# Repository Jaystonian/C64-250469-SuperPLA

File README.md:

# C64-250469-SuperPLA
Replacement board for a 251715-01 or 252535-01

I built one to test and topically it did not work, need to find time to understand why.  I suspect it was the AHCT chips, should use HCT.

Update 2023-04-07 The problem turns out to be the PCB's footprint for the SRAM, as Pin 1 is in the wrong location.

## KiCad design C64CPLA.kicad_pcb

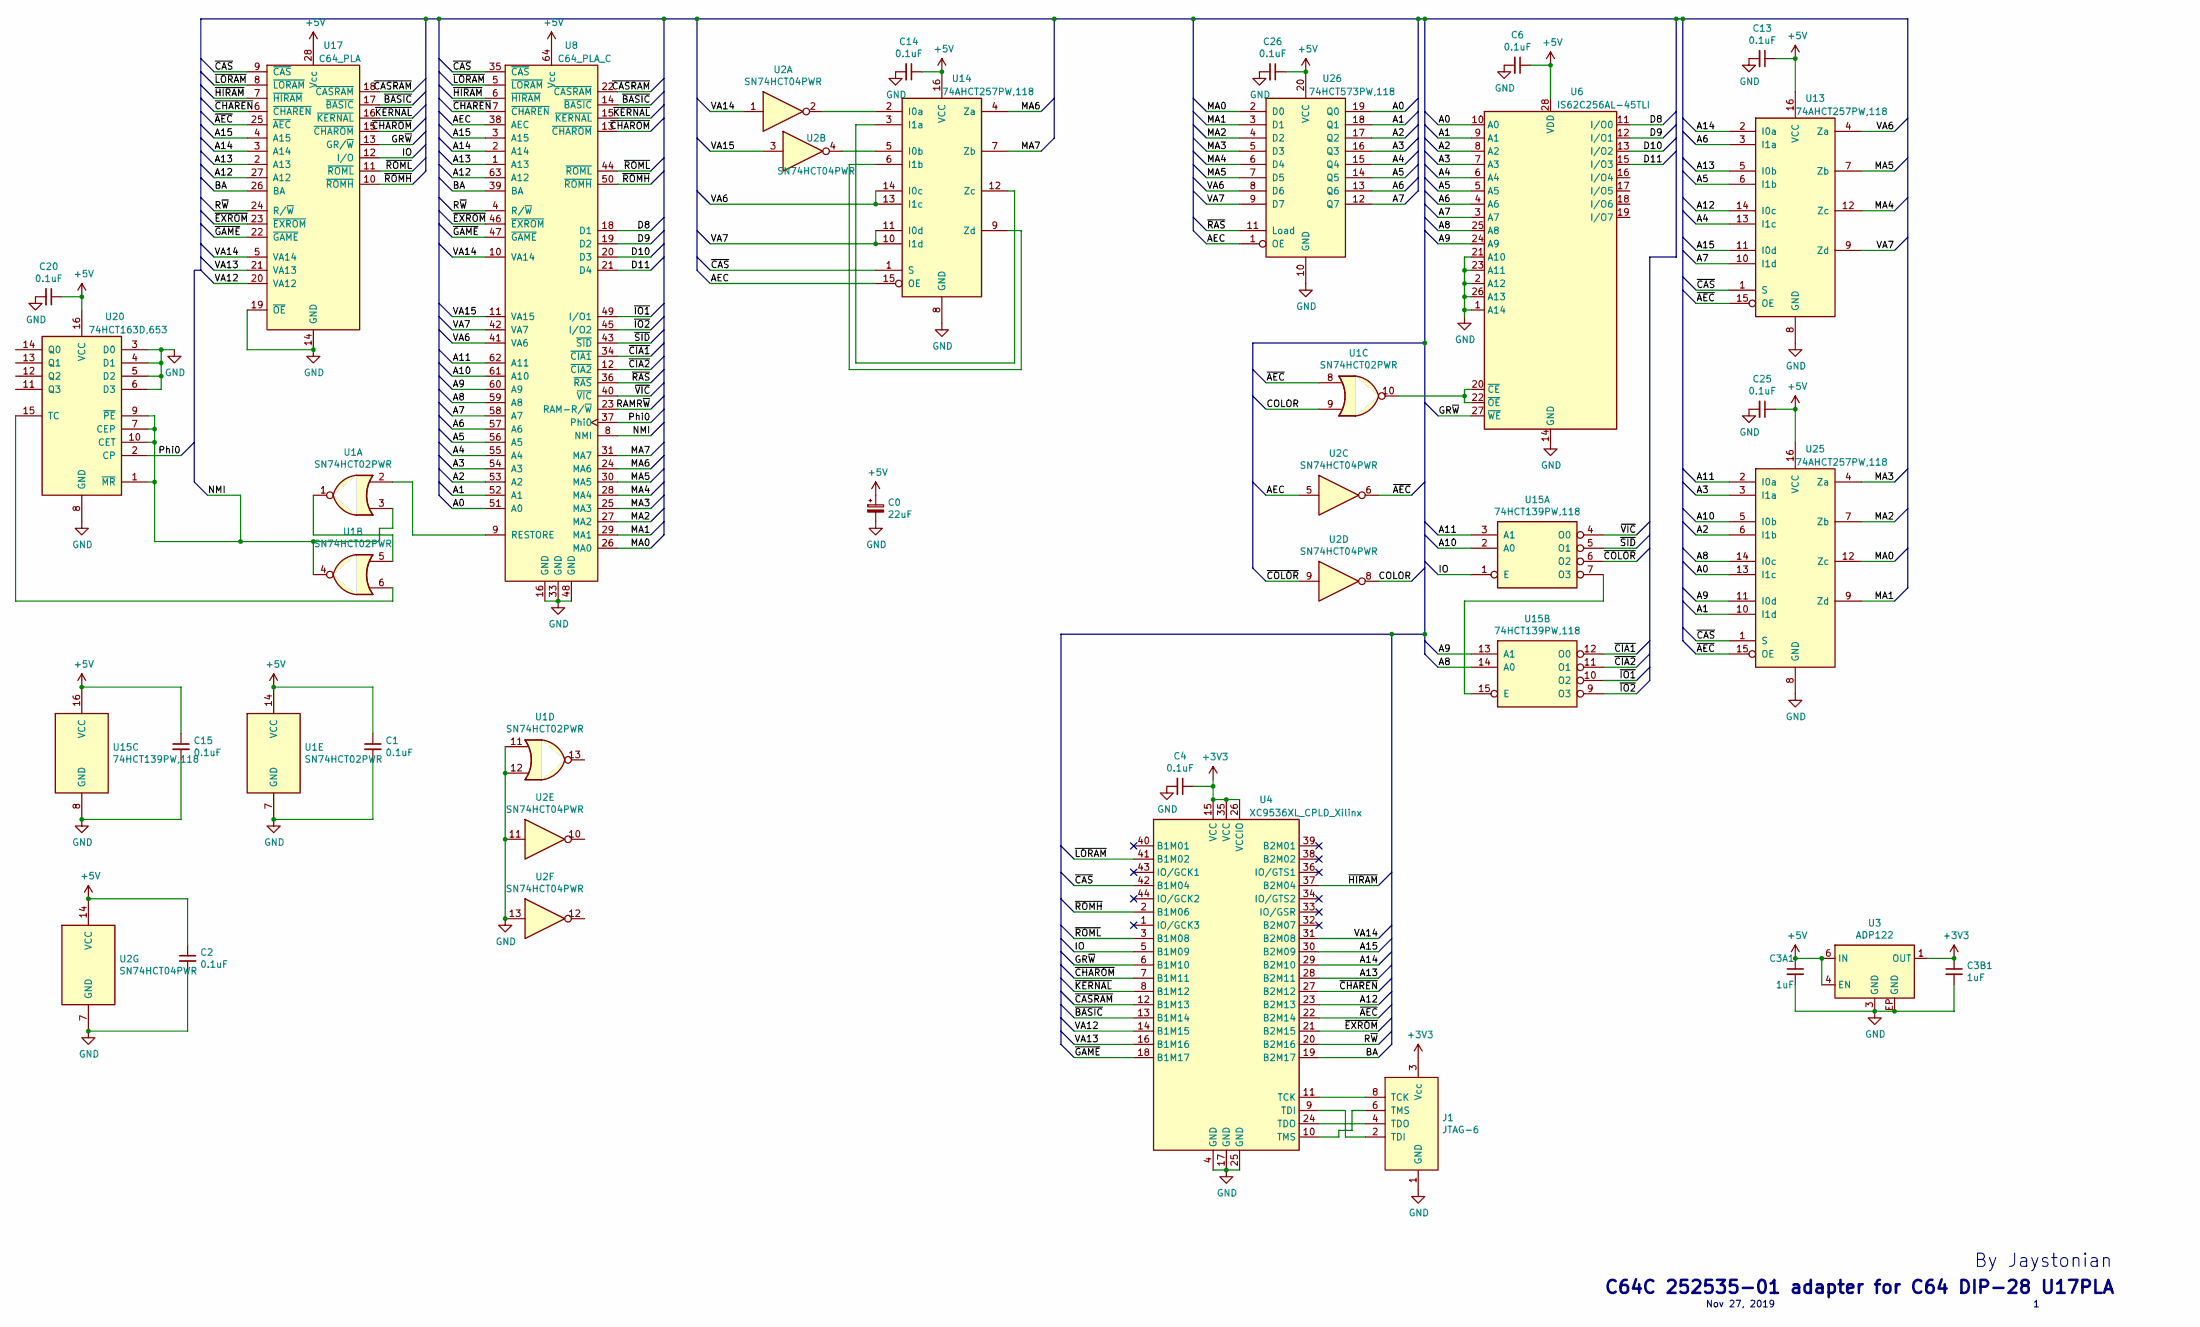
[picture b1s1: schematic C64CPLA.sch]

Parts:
C0: 22uF; CP_EIA-6032-28_Kemet-C_Pad2.25x2.35mm_HandSolder
C1, C2, C4, C6, C13, C14, C15, C20, C25, C26: 0.1uF; R_0805_2012Metric
C3A1, C3B1: 1uF; R_0805_2012Metric
J1: JTAG-6; PinHeader_2x04_P2.54mm_Vertical
U1: SN74HCT02PWR; TSSOP-14_4.4x5mm_P0.65mm
U2: SN74HCT04PWR; TSSOP-14_4.4x5mm_P0.65mm
U3: ADP122; LFCSP-6
U4: XC9536XL_CPLD_Xilinx; TQFP-44_10x10mm_P0.8mm
U6: IS62C256AL-45TLI; TSOP-I-28_11.8x8mm_P0.55mm
U8: C64_PLA_C; DIP-64_750
U13, U14, U25: 74AHCT257PW,118; TSSOP-16_4.4x5mm_P0.65mm
U15: 74HCT139PW,118; TSSOP-16_4.4x5mm_P0.65mm
U17: C64_PLA; DIP-28_W15.24mm
U20: 74HCT163D,653; SOIC-16_3.9x9.9mm_P1.27mm
U26: 74HCT573PW,118; TSSOP-20_4.4x6.5mm_P0.65mm

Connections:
+5V: C0.1, C1.1, C2.1, C3A1.1, C6.1, C13.1, C14.1, C15.1, C20.1, C25.1, C26.1, U1.14 (VCC), U2.14 (VCC), U3.4 (EN), U3.6 (IN), U6.28 (VDD), U8.64 (Vcc), U13.16 (VCC), U14.16 (VCC), U15.16 (VCC), U17.28 (Vcc), U20.16 (VCC), U25.16 (VCC), U26.20 (VCC)
/A0: U6.10 (A0), U8.51 (A0), U25.13 (I1c), U26.19 (Q0)
/A1: U6.9 (A1), U8.52 (A1), U25.10 (I1d), U26.18 (Q1)
/A2: U6.8 (A2), U8.53 (A2), U25.6 (I1b), U26.17 (Q2)
/A3: U6.7 (A3), U8.54 (A3), U25.3 (I1a), U26.16 (Q3)
/A4: U6.6 (A4), U8.55 (A4), U13.13 (I1c), U26.15 (Q4)
/A5: U6.5 (A5), U8.56 (A5), U13.6 (I1b), U26.14 (Q5)
/A6: U6.4 (A6), U8.57 (A6), U13.3 (I1a), U26.13 (Q6)
/A7: U6.3 (A7), U8.58 (A7), U13.10 (I1d), U26.12 (Q7)
/A8: U6.25 (A8), U8.59 (A8), U15.14 (A0), U25.14 (I0c)
/A9: U6.24 (A9), U8.60 (A9), U15.13 (A1), U25.11 (I0d)
/A10: U8.61 (A10), U15.2 (A0), U25.5 (I0b)
/A11: U8.62 (A11), U15.3 (A1), U25.2 (I0a)
/A12: U4.23 (B2M13), U8.63 (A12), U13.14 (I0c), U17.27 (A12)
/A13: U4.28 (B2M11), U8.1 (A13), U13.5 (I0b), U17.2 (A13)
/A14: U4.29 (B2M10), U8.2 (A14), U13.2 (I0a), U17.3 (A14)
/A15: U4.30 (B2M09), U8.3 (A15), U13.11 (I0d), U17.4 (A15)
/AEC: U2.5, U8.38 (AEC), U14.15 (OE), U26.1 (OE)
/BA: U4.19 (B2M17), U8.39 (BA), U17.26 (BA)
/COLOR: U1.9, U2.8
/D8: U6.11 (I/O0), U8.18 (D1)
/D9: U6.12 (I/O1), U8.19 (D2)
/D10: U6.13 (I/O2), U8.20 (D3)
/D11: U6.15 (I/O3), U8.21 (D4)
/GR~W: U4.6 (B1M10), U6.27 (~WE), U17.13 (GR/~W~)
/IO: U4.5 (B1M09), U15.1 (E), U17.12 (I/O)
/MA0: U8.26 (MA0), U25.12 (Zc), U26.2 (D0)
/MA1: U8.29 (MA1), U25.9 (Zd), U26.3 (D1)
/MA2: U8.27 (MA2), U25.7 (Zb), U26.4 (D2)
/MA3: U8.25 (MA3), U25.4 (Za), U26.5 (D3)
/MA4: U8.28 (MA4), U13.12 (Zc), U26.6 (D4)
/MA5: U8.30 (MA5), U13.7 (Zb), U26.7 (D5)
/MA6: U8.24 (MA6), U14.4 (Za)
/MA7: U8.31 (MA7), U14.7 (Zb)
/NMI: U1.3, U1.4, U8.8 (NMI), U20.1 (~MR), U20.7 (CEP), U20.9 (~PE), U20.10 (CET)
/Phi0: U8.37 (Phi0), U20.2 (CP)
/RAMR~W: U8.23 (RAM-R/~W)
/R~W: U4.20 (B2M16), U8.4 (R/~W), U17.24 (R/~W~)
/VA6: U8.41 (VA6), U13.4 (Za), U14.13 (I1c), U14.14 (I0c), U26.8 (D6)
/VA7: U8.42 (VA7), U13.9 (Zd), U14.10 (I1d), U14.11 (I0d), U26.9 (D7)
/VA12: U4.14 (B1M15), U17.20 (VA12)
/VA13: U4.16 (B1M16), U17.21 (VA13)
/VA14: U2.1, U4.31 (B2M08), U8.10 (VA14), U17.5 (VA14)
/VA15: U2.3, U8.11 (VA15)
/~AEC: U1.8, U2.6, U4.22 (B2M14), U13.15 (OE), U17.25 (~AEC), U25.15 (OE)
/~BASIC: U4.13 (B1M14), U8.14 (~BASIC~), U17.17 (~BASIC~)
/~CAS: U4.42 (B1M04), U8.35 (~CAS), U13.1 (S), U14.1 (S), U17.9 (~CAS), U25.1 (S)
/~CASRAM: U4.12 (B1M13), U8.22 (~CASRAM~), U17.18 (~CASRAM~)
/~CHAREN: U4.27 (B2M12), U8.7 (~CHAREN), U17.6 (~CHAREN)
/~CHAROM: U4.7 (B1M11), U8.13 (~CHAROM~), U17.15 (~CHAROM~)
/~CIA1: U8.34 (~CIA1), U15.12 (O0)
/~CIA2: U8.12 (~CIA2), U15.11 (O1)
/~COLOR: U2.9, U15.6 (O2)
/~EXROM: U4.21 (B2M15), U8.46 (~EXROM~), U17.23 (~EXROM~)
/~GAME: U4.18 (B1M17), U8.47 (~GAME~), U17.22 (~GAME~)
/~HIRAM: U4.37 (B2M04), U8.6 (~HIRAM), U17.7 (~HIRAM)
/~IO1: U8.49 (I/O1), U15.10 (O2)
/~IO2: U8.45 (I/O2), U15.9 (O3)
/~KERNAL: U4.8 (B1M12), U8.15 (~KERNAL~), U17.16 (~KERNAL~)
/~LORAM: U4.41 (B1M02), U8.5 (~LORAM), U17.8 (~LORAM)
/~RAS: U8.36 (~RAS), U26.11 (Load)
/~ROMH: U4.2 (B1M06), U8.50 (~ROMH), U17.10 (~ROMH~)
/~ROML: U4.3 (B1M08), U8.44 (~ROML), U17.11 (~ROML~)
/~SID: U8.43 (~SID), U15.5 (O1)
/~VIC: U8.40 (~VIC), U15.4 (O0)
GND: C0.2, C1.2, C2.2, C3A1.2, C3B1.2, C4.2, C6.2, C13.2, C14.2, C15.2, C20.2, C25.2, C26.2, J1.1 (GND), U1.7 (GND), U1.11, U1.12, U2.7 (GND), U2.11, U2.13, U3.3 (GND), U3.EP (GND), U4.4 (GND), U4.17 (GND), U4.25 (GND), U6.1 (A14), U6.2 (A12), U6.14 (GND), U6.21 (A10), U6.23 (A11), U6.26 (A13), U8.16 (GND), U8.33 (GND), U8.48 (GND), U13.8 (GND), U14.8 (GND), U15.8 (GND), U17.14 (GND), U17.19 (~OE~), U20.3 (D0), U20.4 (D1), U20.5 (D2), U20.6 (D3), U20.8 (GND), U25.8 (GND), U26.10 (GND)
unnamed: J1.2 (TDI), U4.9 (TDI)
unnamed: J1.4 (TDO), U4.24 (TDO)
unnamed: J1.6 (TMS), U4.10 (TMS)
unnamed: J1.8 (TCK), U4.11 (TCK)
unnamed: U1.1, U1.5
unnamed: U1.2, U8.9 (RESTORE)
unnamed: U1.6, U20.15 (TC)
unnamed: U1.10, U6.20 (~CE), U6.22 (~OE)
unnamed: U2.2, U14.2 (I0a)
unnamed: U2.4, U14.5 (I0b)
unnamed: U14.6 (I1b), U14.9 (Zd)
unnamed: U14.3 (I1a), U14.12 (Zc)
unnamed: U15.7 (O3), U15.15 (E)

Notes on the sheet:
C64C 252535-01 adapter for C64 DIP-28 U17PLA
Nov 27, 2019
By Jaystonian

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
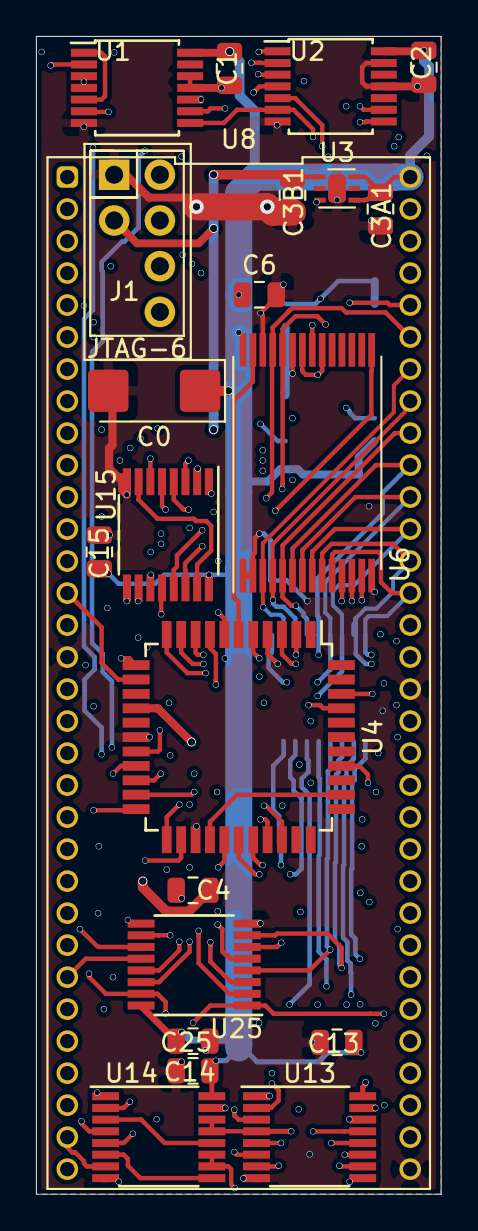
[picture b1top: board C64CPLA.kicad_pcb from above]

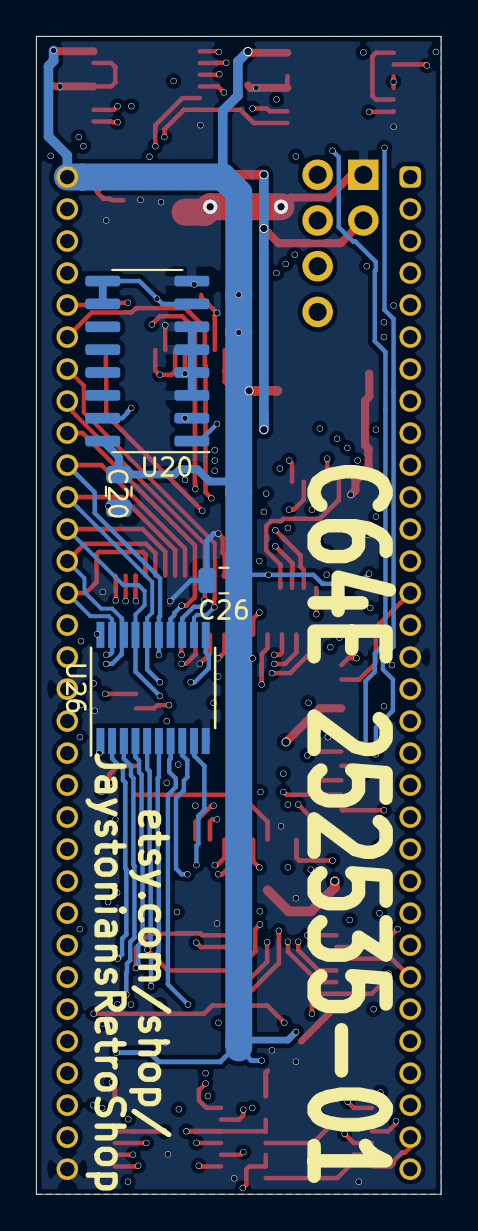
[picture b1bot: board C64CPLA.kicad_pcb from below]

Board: 6 copper layers, 22.5 x 64.3 mm, 26 parts (4 on the bottom side), 78 nets.
